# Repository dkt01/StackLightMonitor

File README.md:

# StackLightMonitor

[hackaday.io Project Page](https://hackaday.io/project/26995-stack-light-monitor)

Demo video

Jenkins monitor using industrial stack light as output

## Software Dependencies

The following packages are necessary to run this software:

+ [EtherCard](https://github.com/jcw/ethercard): Driver for ENC28J60 Ethernet controller on Arduino microcontrollers
+ [SparkFun Arduino_Boards](https://github.com/sparkfun/Arduino_Boards): Support for Arduino Pro Micro in Arduino IDE
+ [HTMLMinifier](https://github.com/kangax/html-minifier): HTML and Javascript minifier to reduce html page size.
+ [ImageMagick](http://www.imagemagick.org/script/index.php): Image conversion tool to create favicon.ico file from svg source.

## Attribution

Favicon is a derivative of ["Database" by Tinashe Mugayi](https://thenounproject.com/search/?q=database&creator=1554334&i=955064).  It is covered by the [Creative Commons 3.0 Attribution License](https://creativecommons.org/licenses/by/3.0/us/).

Config page uses CSS from [Pure CSS](https://purecss.io).  It is covered by the [Yahoo! BSD License](https://github.com/yahoo/pure-site/blob/master/LICENSE.md).

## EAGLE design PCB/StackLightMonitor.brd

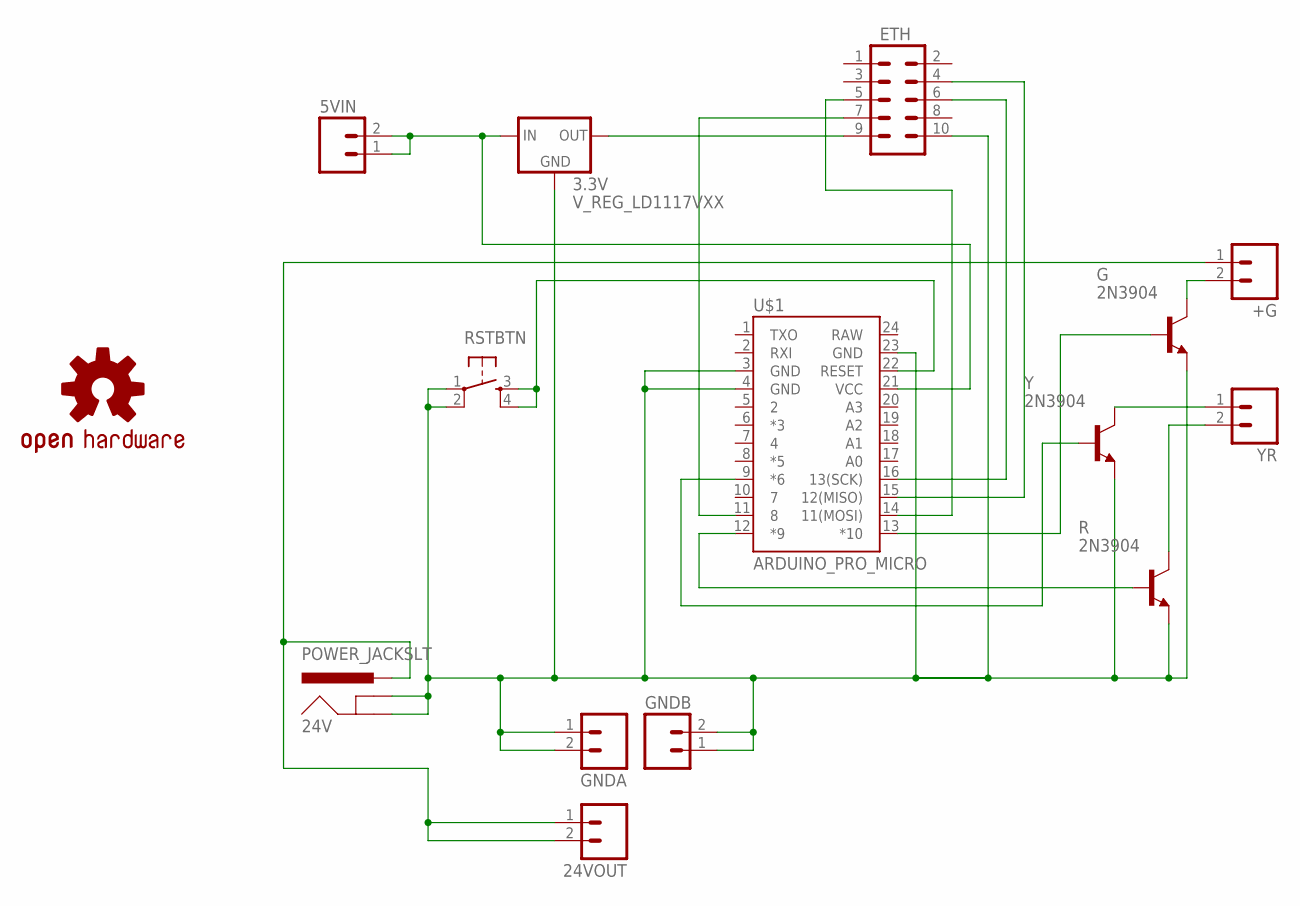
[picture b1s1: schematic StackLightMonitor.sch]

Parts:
3.3V: V_REG_LD1117VXX; 78XXL
5VIN, 24VOUT: M02PTH; 1X02
24V: POWER_JACKSLT; POWER_JACK_SLOT
+G: M025MM; SCREWTERMINAL-5MM-2
ETH: M05X2PTH; AVR_ICSP
G: 2N3904; TO92
GNDA: M02PTH; 1X02
GNDB: M02PTH; 1X02
LOGO1: OSHW-LOGOL; OSHW-LOGO-L
R: 2N3904; TO92
RSTBTN: TAC_SWITCHPTH; TACTILE-PTH
U$1: ARDUINO_PRO_MICRO
Y: 2N3904; TO92
YR: M025MM; SCREWTERMINAL-5MM-2

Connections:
5V: 3.3V.OUT (IN), 5VIN.1, 5VIN.2, U$1.21 (VCC)
24V: 24V.PWR, 24VOUT.1, 24VOUT.2, +G.1
33V: 3.3V.GND (OUT), ETH.9
CS: ETH.7, U$1.11 (8)
G: G.2 (B), U$1.13 (*10)
GGND: +G.2, G.1 (C)
GND: 3.3V.IN (GND), 24V.GND@1 (GNDBREAK), 24V.GND@2 (GND), ETH.10, G.3 (E), GNDA.1, GNDA.2, GNDB.1, GNDB.2, R.3 (E), RSTBTN.1, RSTBTN.2, U$1.3 (GND), U$1.4 (GND), U$1.23 (GND), Y.3 (E)
MISO: ETH.4, U$1.15 (12(MISO))
MOSI: ETH.5, U$1.14 (11(MOSI))
R: R.2 (B), U$1.12 (*9)
RESET: RSTBTN.3, RSTBTN.4, U$1.22 (RESET)
RGND: R.1 (C), YR.2
SCK: ETH.6, U$1.16 (13(SCK))
Y: U$1.9 (*6), Y.2 (B)
YGND: Y.1 (C), YR.1

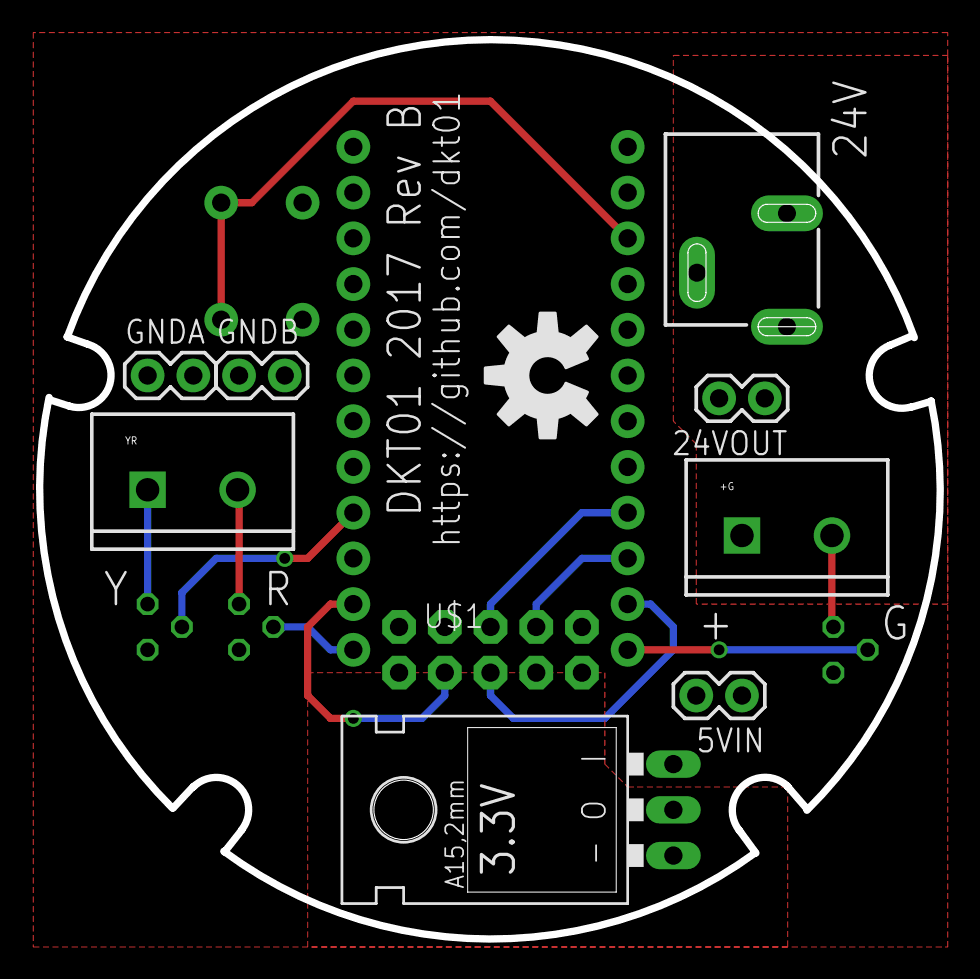
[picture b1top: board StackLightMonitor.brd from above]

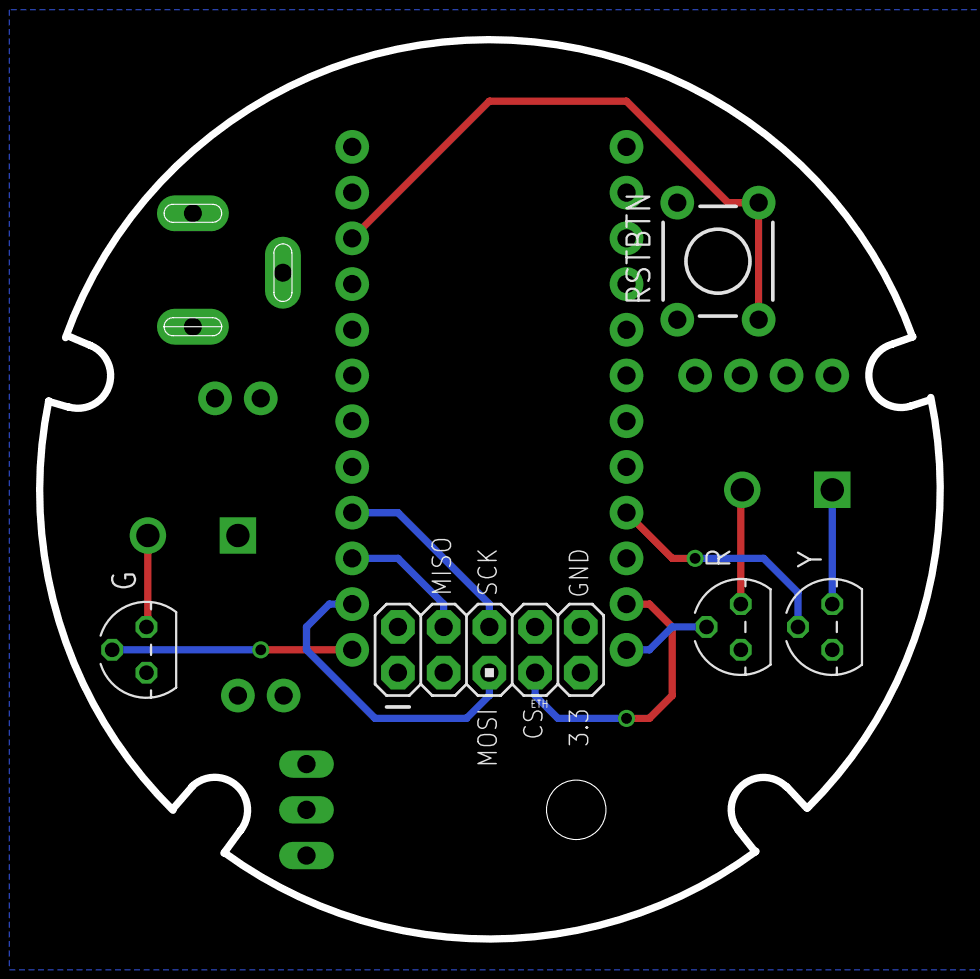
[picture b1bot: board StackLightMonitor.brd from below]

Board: 2 copper layers, 50.0 x 50.0 mm, 15 parts (5 on the bottom side), 15 nets.

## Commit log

2017-04-09 Added PCB files
2017-04-09 Added some CAD files
2017-04-10 Possibly complete CAD
2017-04-11 Updated CAD for 3D printing. Fixed some constraints that were broken
2017-04-26 Updated silkscreen
2017-05-01 Test sequences working on hardware
2017-05-01 Create .codedocs file
2017-05-03 Began configuration webpage
2017-05-03 Updates to config webpage
    + Removed fetch api to support older browsers
    + No longer require CORS support from API servers
    + Some style changes
    + Job endpoint validation to support sending good address to Arduino
2017-05-04 Removed jsonp dependency. Added existing configuration query. Added configuration saving.
2017-05-05 Added preliminary ethernet support
2017-05-06 Added minifier script and updated readme with dependency information
2017-05-06 Delinting
2017-05-06 Added support for multi-packet HTTP responses
2017-05-06 Added support for CORS proxy to overcome cross-site request issues
2017-05-06 Added favicon support and fixed apiURL request endpoint address
2017-05-07 Made favicon transparent background Added apiURL save and load functions Fixed webpage onload function to actually do something
2017-05-09 Moving URL parsing to javascript
2017-05-10 Finished support for web client URL parsing
2017-05-16 DNS lookup working. Pre-initialization now has all lights on instead of off
2017-05-16 Fixed config PUT request handling
2017-05-24 Saved ~2.3KB flash by gzip compressing favicon and config site
2017-05-25 Sending API queries to Jenkins, but only printing returned value
2017-06-11 Added support for both CORS proxy and non-CORS proxy Jenkins servers in config webpage.
2017-06-11 Fixed support for multi-packet PUT requests
2017-08-06 Now parses JSON returns and illuminates according to status
2017-08-11 Added doxygen file headers with license info
2017-08-13 Beautified config webpage :)
2017-08-13 Fixed bug where HTTP server changed port to the port of the Jenkins server.
2017-08-28 Added links to demo video and project details in readme

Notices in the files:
parts and their libraries:
SparkFun-Connectors: Licensing: Creative Commons ShareAlike 4.0 International - https://creativecommons.org/licenses/by-sa/4.0
